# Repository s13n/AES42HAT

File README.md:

# AES42HAT

The AES42HAT is a Raspberry Pi compatible HAT with up to 4 channels of
AES3/AES42 interface. At present it is a work in progress.

AES3 is the stereo digital audio interface for professional applications, which
is compatible to some extent with SPDIF as used on consumer gear.

AES42 is building on AES3 to provide power and control for digital microphones.

Depending on what is fitted on the board, AES42HAT supports up to 4 stereo
channels of input/output, with or without SRC on input, and with or without
external synchronization.

Raspberry Pi models up to the Raspberry Pi 4B, and various clones, support only
one stereo channel in/out. The Raspberry Pi 5 supports the full set of 4 stereo
channels. The BeagleY-AI also supports 4 stereo channels in/out.

The 4 inputs and outputs are available on a header that supports the "Tascam
pinout" (or AES59 pinout) for a 25-pin SubD connector for multichannel digital
input/output. A standard IDC cable adapter between the header and the SubD
connector is needed.

## Build variants

The design supports different variants, depending on which parts are fitted on
the board. This allows a tradeoff between cost and feature set, depending on
user's needs.

See the schematics for the function blocks that can be omitted if desired. The
bare minimum consists of the parts that are shown outside of an optional block.

The Raspberry Pi uses the ID EEPROM to determine the build variant.

### Minimum build -- AES42HAT lite

The minimum build uses a DIX4192 for U10, and omits everything in the optional
blocks. It provides a stereo input/output in AES3 format, without SRC. It is
compatible with most Raspberry Pi models and some clones, provided they feature
a PCM interface on the standard pins, and a finely adjustable clock source on
GCLK0. It offers minimal cost for stereo applications that don't need AES42
support or SRC.

The lack of SRC means that there are only two sensible clocking options:

- The Raspberry Pi supplies the clock, and both input and output use it. This
  can be useful when an external device is connected, that synchronizes to the
  signal it receives from the AES42HAT.
- The output uses the clock derived from the received signal. This is useful
  when the external device is treated as the clock source, and the Raspberry is
  following it.

In both cases input and output use the same clock, i.e. they are synchronous to
each other.

The lack of a clock synthesizer means that the HAT is dependent on the Raspberry
Pi for a clock source. The original Raspberry Pi contains finely tunable PLLs
which can output a clock signal on GCLK0 that acts as a clock master. If a clone
doesn't support this, it won't work.

The lack of a control processor means that the DIX4192 is configured and
controlled directly by the Raspberry Pi through its SPI0 interface.

### Full-featured stereo interface -- AES42HAT stereo

This is the AES42HAT lite with an SRC4392 for U10, plus the clock synthesizer.

This adds the capability of using SRC on input, so the input clock can be
independent from the output clock. The presence of a clock synthesizer
eliminates the dependency on the Raspberry Pi clock generator, and adds a
separate wordclock input and output to support synchronization.

The clock syntheziser may also be slaved to a 10 MHz reference input as commonly
used in measurement equipment and frequency references. This can be used for
measurement purposes, or for creating audio clocks from GPS receivers and highly
stable oscillators.

The clock synthesizer is controlled by the Raspberry Pi through its I2C bus.

### Full-featured 8-channel interface -- AES42HAT octal

This adds 3 more stereo channels to the AES42HAT stereo to form a bidirectional
8-channel interface. SRC is supported on all channels by virtue of 3 more
SRC4392 chips, so that each input can run on its own clock, while all outputs
share a common clock generated by the local clock synthesizer.

The addition of more channels also requires the local control processor. The
SPI0 interface on the Raspberry Pi is no longer needed. All control is done via
the I2C bus, with the control processor managing the multiple channels.

Any of the input channels can be used as a synchronization source, instead of
the separate wordclock input.

The usage of a Raspberry 5 or a BeagleY-AI is needed to handle all the audio
channels.

### Full-featured 8-channel interface with AES42 support -- AES42HAT microphone

This adds AES42 compatible phantom power and remote control capability to all 4
stereo input channels of the AES42HAT octal. All synchronization modes of AES42
are supported, and the microphones can be remote controlled, independently for
each of the 4 inputs.

This requires a power supply that can deliver the necessary current for powering
the microphones in addition to the Raspberry Pi with the HAT. It is recommended
to use a 25W power supply capable of delivering 5A@5V to the Raspberry Pi 5.
Appropriate cooling should be provided.

The local control processor takes care of the AES42 specifics, and the Raspberry
Pi controls and monitors it via I2C.

If the goal is to merely power and control AES42 microphones, whose audio signal
is made available on the AES3 outputs, with no intent to process the audio with
the Raspberry Pi, then a cheaper/smaller Raspberry Pi can be used, for example a
Pi Zero 2. When intending to process the audio with the Raspberry Pi, use a
Raspberry Pi 5 or a BeagleY-AI.

## Function blocks

### Power Supply and Reset

The AES42HAT is powered through the HAT connector's 5V supply. Only the board ID
EEPROM (U3) is powered from the 3.3V supply on the HAT connector (J1). A dual
DC/DC converter (U4) generates local 3.3V and 1.8V rails for most of the
electronics on the board. The DC/DC converter is enabled by the 3.3V supply from
the HAT connector, so when the Raspberry Pi is powered down, the AES42HAT is
also powered down, even though the 5V rail may remain on.

The Raspberry Pi is responsible for lifting the RESET line after powerup,
otherwise the AES42HAT will remain in reset due to R5 pulling down the RESET
line. The ID EEPROM can be accessed regardless if the board is in reset or not.

### Local Control Processor (optional)

The 8-channel variants of the AES42HAT have a local control processor (U1)
fitted, which configures and controls the receivers and transmitters, and
handles the phantom powering, the remote control and the synchronization of the
AES42 interfaces.

The Raspberry Pi accesses the control processor primarily through I2C, using
pins 3&5 on the HAT connector. The Raspberry Pi controls this interface, and the
AES42HAT is the target. The communication protocol is TBD.

There is also a UART connection between the Raspberry Pi and the control
processor on pins 8&10. This connection can be used for updating the firmware of
the control processor from the Raspberry Pi. It may also be used during normal
operation for a console-like communication interface. The details are TBD.

There is an additional signal on Pin 26 of the HAT connector (REQ/ISP), which
serves two purposes:

- Upon release of RESET, the signal determines the boot mode of the control
  processor. When high, the control processor boots normally and executes its
  stored firmware. When low, it boots into a bootloader that can be used to
  update its firmware through the UART interface. Hence, to initiate firmware
  update, the Raspberry PI has to pull this signal low while releasing RESET.
- During normal operation, the signal is used as a service request signal from
  the AES42HAT to the Raspberry Pi. It is up to the Raspberry Pi to poll the
  signal, or arrange for an interrupt to be generated whenever the signal goes
  low. The control processor holds the interrupt active until the Raspberry Pi
  clears it through the I2C interface. The details are TBD.

When the control processor is fitted, the Raspberry Pi's own SPI interface on
HAT connector pins 19,21,23&24 is not used and must be disabled.

### Clock Synthesizer (optional)

The clock synthesizer supports generating arbitrary audio clock frequencies, and
to reference them to an external clock source. This provides considerable
flexibility in setting up the clocking structure of a system. The following
features are supported:

- Support for any sampling rate the Receivers/Transmitters are capable of (20 ..
  216 kHz). All transmitters use the same rate, and are synchronous to each
  other.
- Sampling rate can be finely tuned by software.
- An external 10 MHz reference can be connected to support synchronization from
  highly stable frequency sources (GPS receivers, OXCOs, Rubidium sources, ...).
  This can also help measurement applications. If no external reference is used,
  an internal 10 MHz crystal is used. The reference signal can be made available
  internally as the ACLK signal.
- Any one of the AES3 input signals can be used as the synchronization source.
- An external TTL wordclock signal can be connected to serve as a
  synchronization source.
- A TTL wordclock output is available.

All those features are controlled from software. The clock synthesizer is
connected to the I2C bus (HAT connector pins 3&5) that is controlled by the
Raspberry Pi. It produces two output clocks:

- The MCLK signal is the audio master clock from which the transmitters derive
  their output signal. The audio interface of the Raspberry Pi (PCM) is also
  driven from this clock, and operated in slave mode. The MCLK signal connects
  to pin 7 of the HAT interface. This allows the Raspberry Pi to supply the
  audio master clock instead of the clock synthesizer. The clock synthesizer's
  output must be switched off in this case (if it is fitted).
- The ACLK signal is typically driven by the 10 MHz reference clock signal. It
  can be used in the AES3 receivers as a reference signal for measuring incoming
  sampling rates.

The MCLK frequency should be between 10 and 25 MHz. For a single-speed sampling
rate up to a nominal 48 kHz, MCLK should be 512 * Fs. For a double-speed rate up
to 96 kHz it should be 256 * Fs. For a quad-speed rate up to 192 kHz it should
be 128 * Fs. The dividers in U10 must be set up to divide this down to the right
bit clock and word clock.

The clock synthesizer has a separate synchronization input that is driven by the
RCLK signal. Its use is optional, determined by software.

- If RCLK is not used, the 10 MHz signal is used as the reference, from which
  MCLK is derived directly using a fractional PLL.
- If RCLK is used, MCLK is derived from it by steering the fractional multiplier
  of the PLL to track the frequency of RCLK. This also reduces the jitter that
  may be present on RCLK. A wide frequency range on RCLK is supported (50 Hz ..
  30 MHz). Skipped pulses on RCLK can also be supported.

The RCLK signal can be fed from different sources:

- In the default case, it is fed from the external wordclock input. This is a
  TTL level signal that need not work at the wordclock frequency. It may be used
  to synchronize to a wide range of external frequency sources. The Raspberry Pi
  must enable it by driving the WIEN signal low.
- It can alternatively be fed from one of the receivers, using their RXCKO
  output. This output can be enabled to provide a clock signal derived from the
  incoming AES3 signal. It allows an incoming audio signal to be used as the
  synchronization source for the clock synthesizer. On 8-channel variants of
  AES42HAT, only one of four receiver chips can have this output enabled, or
  they will interfere with each other, potentially leading to damage. The output
  is disabled by default. Before enabling one of them, the Raspberry Pi must
  disable the external wordclock signal by driving the WIEN signal high.
- The Raspberry Pi can drive the RCLK signal using its GCLK2/GPIO6 signal on pin
  31 of the HAT connector. Both the wordclock input and the receiver RXCKO
  outputs must be disabled before the Raspberry Pi can activate this signal.

The clock syntheizer can be a CS2000 (obsolete), a CS2500 or a THAT7200. Its I²C
address is 0x4F (0x9E for write, 0x9F for read).

### AES Receivers/Transmitters

Decoding and encoding of the AES3 signal is done by U10 (on 8-channel variants
also U20, U30 and U40). There are three pin-compatible chips that can be fitted
alternatively:

- The **DIX4192** is a receiver and transmitter for one AES3 signal, including
  the balanced driver and receiver necessary for the physical interface.
- The **SRC4392** includes a sampling rate converter (SRC) that can be used with
  either the receiver or the transmitter, but is most useful with the receiver.
  Its other functions are the same as with the DIX4192, and the software
  interface is compatible.
- The **SRC4382** saves some cost by including a less accurate SRC that offers
  worse signal to noise. While this chip can be used, the cost savings are
  usually not worth it, and the AES42HAT will only use it upon special request.

Whichever chip is fitted, most of the functionality is the same. It has an
extensive register set for controlling the details of operation, which is
accessed through an SPI compatible interface.

When the local control processor is fitted, it is in control of the SPI
interface used to configure and control the receivers/transmitters.

The chips have flexible internal signal routing and clocking, which is set up
through the SPI control interface. Routing and clocking is set up as follows:

- U10 is the clock master on the PCM interface to the Raspberry Pi. Audio port A
  is configured in master mode and produces the BCLK and LR clock signals, with
  MCLK as the clock source. The BLS pin is configured as output.
- When fitted, U20, U30 & U40 operate their audio ports A&B in slave mode, so
  the BCKA, BCKB, LRCKA and LRCKB pins are inputs. The BLS pin is also
  configured as input.
- The transmitters within U10, U20, U30 and U40 are typically configured to be
  sourced from audio port A. The transmitter thereby sends an audio signal
  provided by the Raspberry Pi.
- Alternatively, the received input signal can be passed through to the output
  directly, using the pin multiplexers, bypassing the DIR and DIT blocks.
- The SRC is used with the receiver to convert the sampling rate of the received
  signal to the clock used on port A. If the input signal is known to be
  synchronous with this clock, the SRC can be omitted from the signal path.
- The ACLK signal (nominally 10 MHz) is available on the RXCKI signal, and can
  be used as a reference for the SRC to estimate the ratio. It can also be used
  as a reference clock for the DIR block. When the clock synthesizer is not
  fitted, the ACLK signal is not available, and the MCLK signal must be used as
  a reference.

Each receiver/transmitter has 4 GPO pins that have programmable functionality.
On the AES42HAT, they are used as follows:

- **GPO1** is used to enable phantom power for the AES42 input. If the AES42
  circuit is not fitted, the signal is unused. The output defaults to low after
  reset, thereby turning phantom power off.
- **GPO2** is used to select between two synchronization modes of AES42. This is
  only relevant when phantom power is switched on. A low signal selects mode 2,
  which is the default after reset.
- **GPO3** is connected to the control processor, and is intended to carry the
  reconstructed wordclock signal from the receiver ("Receiver Internal Sync
  Clock"). If the control processor is not fitted, the signal is unused.
- **GPO4** is connected to the control processor, and is intended to carry the
  received U-bit ("Receiver User Data Bit"), giving the control processor an
  alternate way to process the incoming user bit. If the control processor is
  not fitted, the signal is unused.

If the intended functionality of GPO3&4 is not required, other signals may be
chosen to be fed to the control processor.

Each receiver/transmitter can generate an interrupt signal. The interrupt signal
is handled by the control processor, if it is fitted. Otherwise the interrupt
from U10 is fed to the Raspberry Pi on HAT connector pin 26.

### AES42 Phantom Supply and Remote Control

AES42 defines a way of powering a connected microphone using a 10 V phantom
power scheme. Additionally, remote control signals can be sent to the microphone
by modulating them on top of the phantom power. The "AES42HAT microphone", the
fully featured variant, supports both.

Phantom power is generated by a DC/DC converter (U51, U61, U71, U81). Each input
can be powered separately, controlled by GPO1 of the respective
receiver/transmitter. The DC/DC converter works from the +5V rail, and each
circuit potentially draws up to 600mA from this rail, depending on the load
represented by the microphone that is connected. The power supply used must be
able to deliver this amount of current.

The control processor can monitor the phantom voltage through signals PVx, so it
can diagnose short circuits or overload.

Remote control using AES42 Mode 2 is handled by raising the phantom voltage for
each pulse generated. This is achieved by temporarily switching the DC/DC
converter to output 12 V instead of 10 V. Edge speed is shaped by an additional
driver (U52, U62, U72, U82).

Mode 3 is supported by a different circuit built from a signal transformer (L50,
L60, L70, L80) driven by a bandpass amplifier (U53, U63, U73, U83). It is based
on a clock signal WCLK generated by the control processor.

For both modes, the modulating signal (MODx) is generated by the control
processor. Switches (U50, U60, U70, U80) are used to select between the two
modes, depending on signals M3x sourced by GPO2 of the receiver/transmitter.

An LED shows the presence of phantom power on each channel. Its brightness is
modulated by the remote control pulses.

### Dependencies Between Optional Function Blocks

The control processor must be fitted if any of U20, U30 or U40 are fitted. It
must also be fitted when the AES42 circuitry is fitted.

The clock synthesizer is controlled by the Raspberry Pi and can be fitted
without the control processor. The clock synthesizer is independent from any
other function block and can be fitted or omitted, regardless of which other
options are fitted. However, if not fitted, the Raspberry Pi must supply the
audio master clock (GCLK0).

## Support for Raspberry Pi Variants and Clones

The AES42HAT is fully compatible with the Raspberry Pi 5, including support for
up to 8 channels of audio input and output.

Previous models of the Raspberry Pi up to the 4B only support stereo audio. The
8-channel variants of AES42HAT can therefore not be fully supported, i.e. the
audio signals of the additional channels can't be accessed by the Raspberry Pi.
The additional channels can be controlled and configured, however, so it is
possible to support use cases where the audio signals need not be touched by the
Raspberry Pi (for example using pass-through from input to output, without or
with SRC).

Raspberry Pi clones may or may not support the PCM interface, so it is up to the
user to check compatibility. In many cases only stereo is supported, if at all.

### BeagleY-AI

The BeagleY-AI is a clone that can support all 8 channels, albeit with some
special arrangements. The pin assignment for the PCM interface is only partly
compatible with the Raspberry Pi 5, and AES42HAT contains some additional wiring
to make up for the difference.

With the BeagleY-AI, the McASP0 is used for all the input signals with up to 8
channels. The output channels are generated by McASP1 and McASP2 in SPDIF
transmit mode. The latter is necessary because of limitations of clock signal
connectivity. The input multiplexers in the receivers/transmitters are used to
route the output signals directly to the balanced line driver, bypassing the DIT
block. To deal with wiring differences for input channels, audio port B is used
on U30 and U40.

### ESP32-P4 Function Evaluation Board

The Espressif ESP32-P4 is a microcontroller with a dual-core RISC-V CPU and a
rich set of peripherals, including I2S and 100 MBit/s Ethernet. It appears to
have some potential for a very low cost platform for low-end networked audio
devices, below the price point of a Linux-based solution. Its evaluation board
has a set of GPIO signals routed to a Raspberry Pi HAT connector. This opens the
possibility to use the AES42HAT as an audio interface.

The ESP32-P4 has 3 I2S function blocks that can be freely assigned to GPIO pins,
and it includes a PLL dedicated for audio. It therefore should be able to work
with the AES42HAT directly, with no need for a wiring change. At the time of
writing, the information available for the ESP32-P4 is sparse, hence the
suitability is somewhat unclear at this point, but it certainly looks promising.

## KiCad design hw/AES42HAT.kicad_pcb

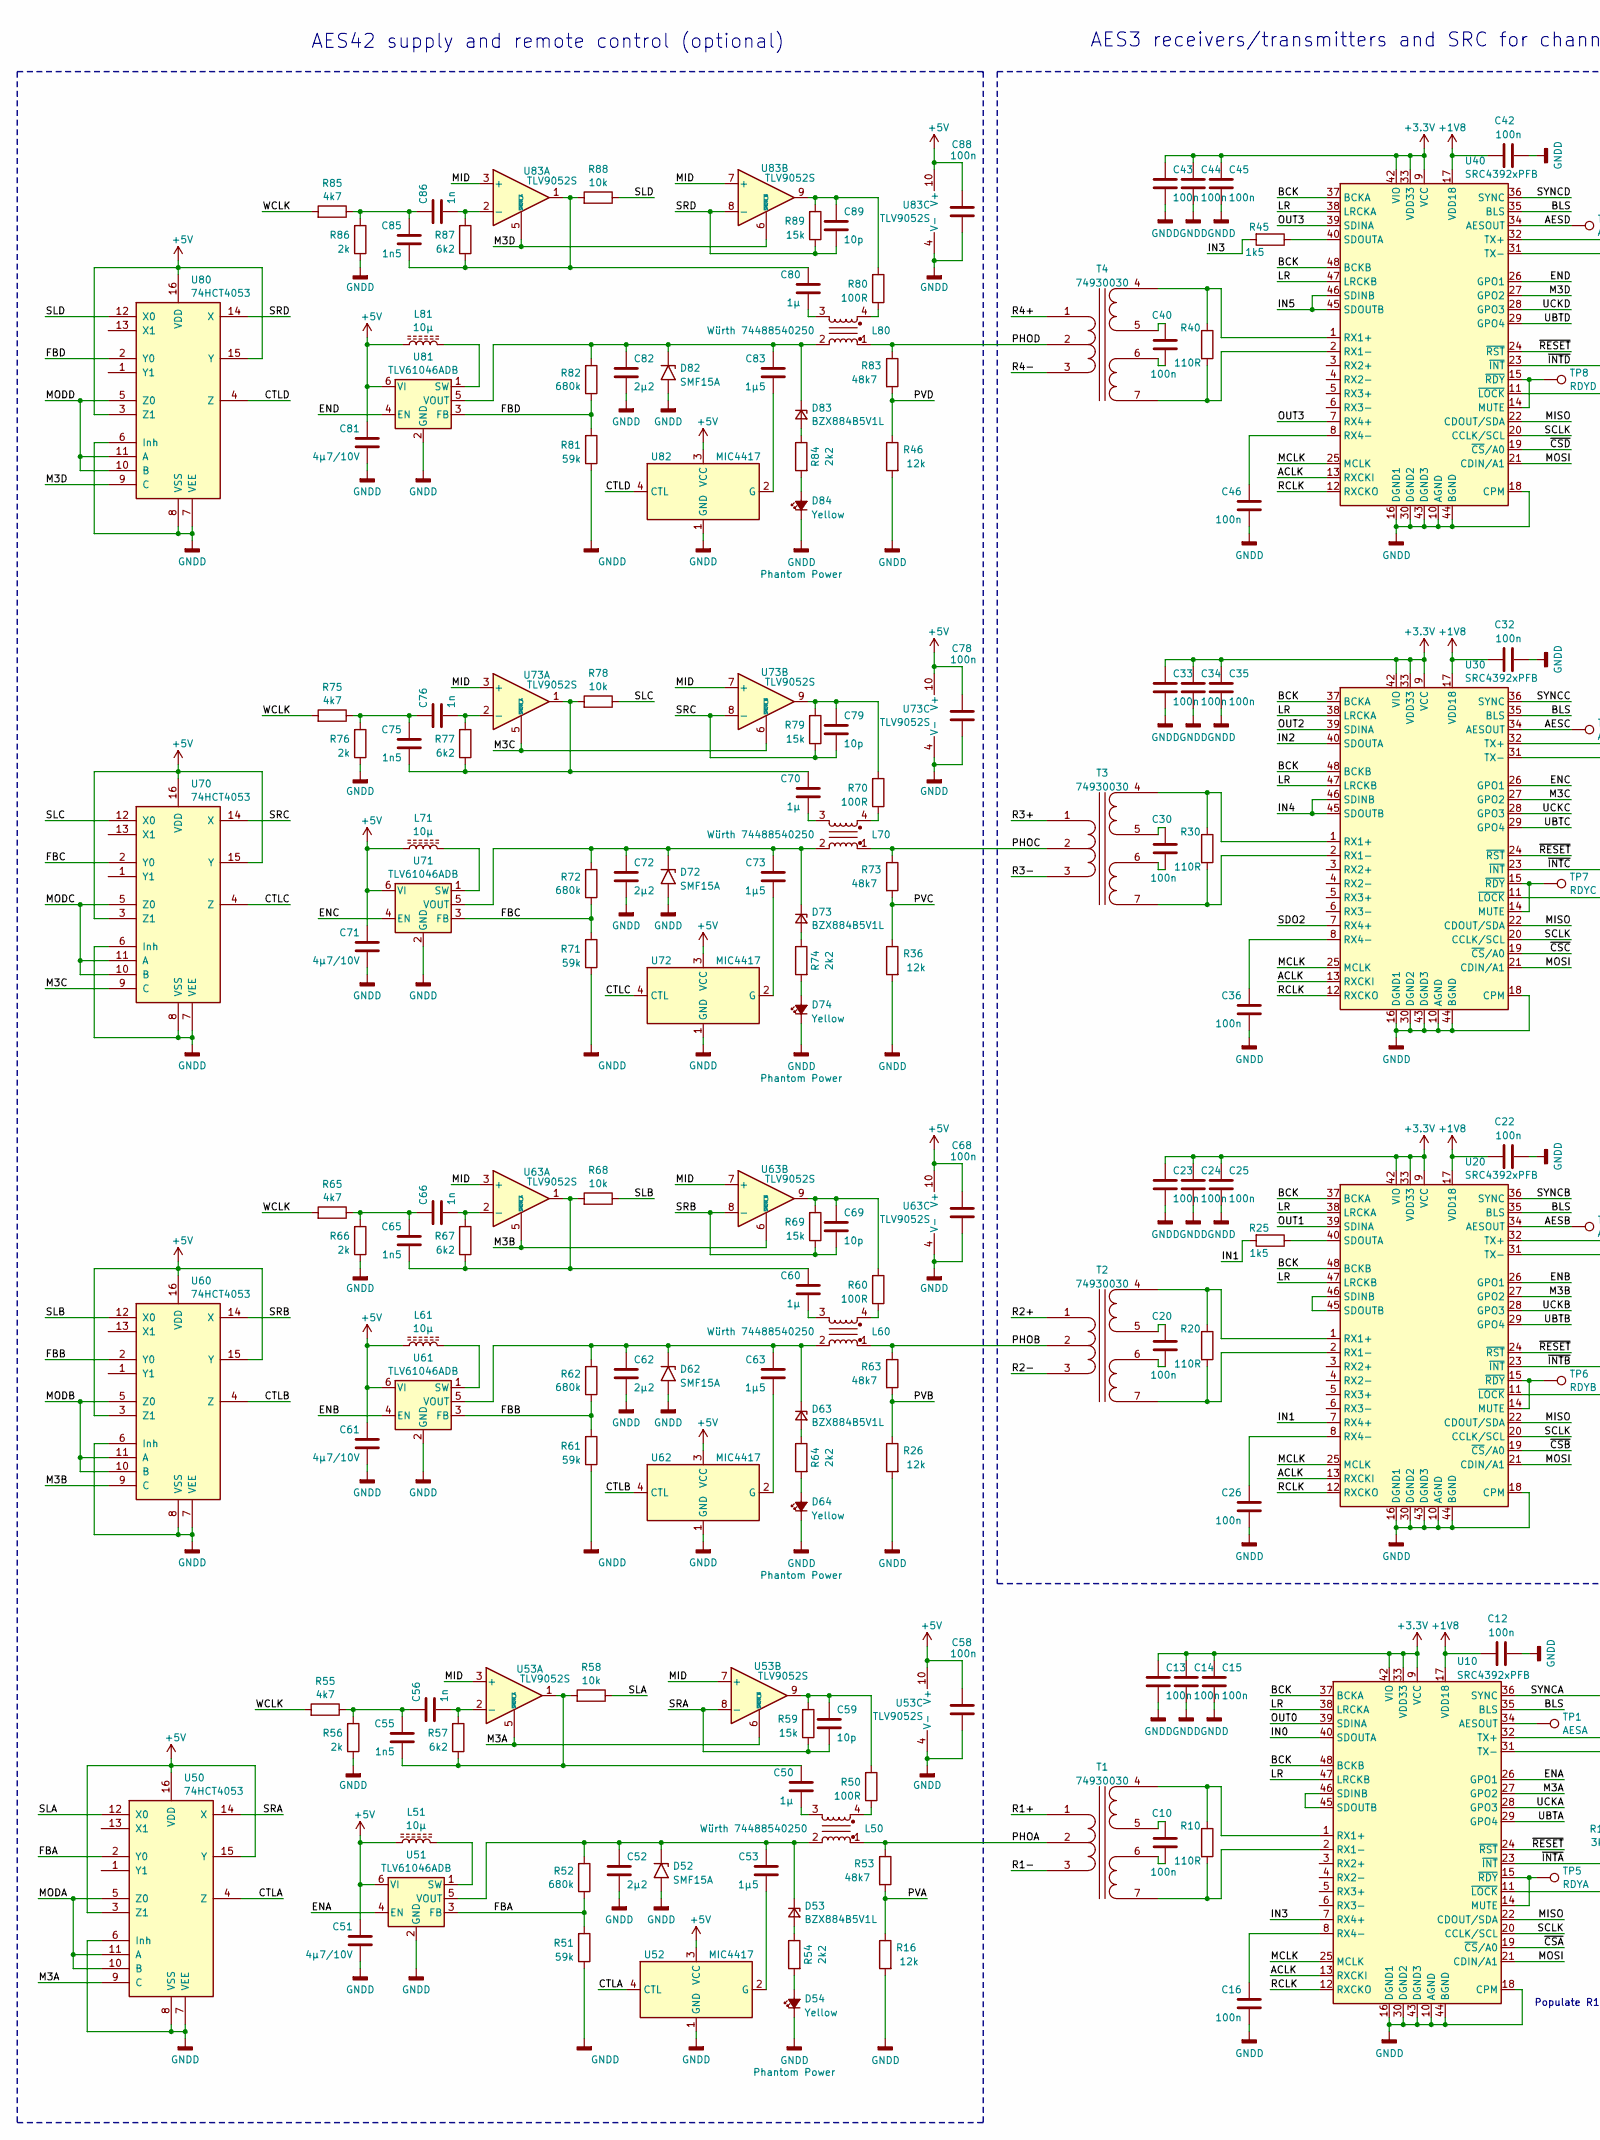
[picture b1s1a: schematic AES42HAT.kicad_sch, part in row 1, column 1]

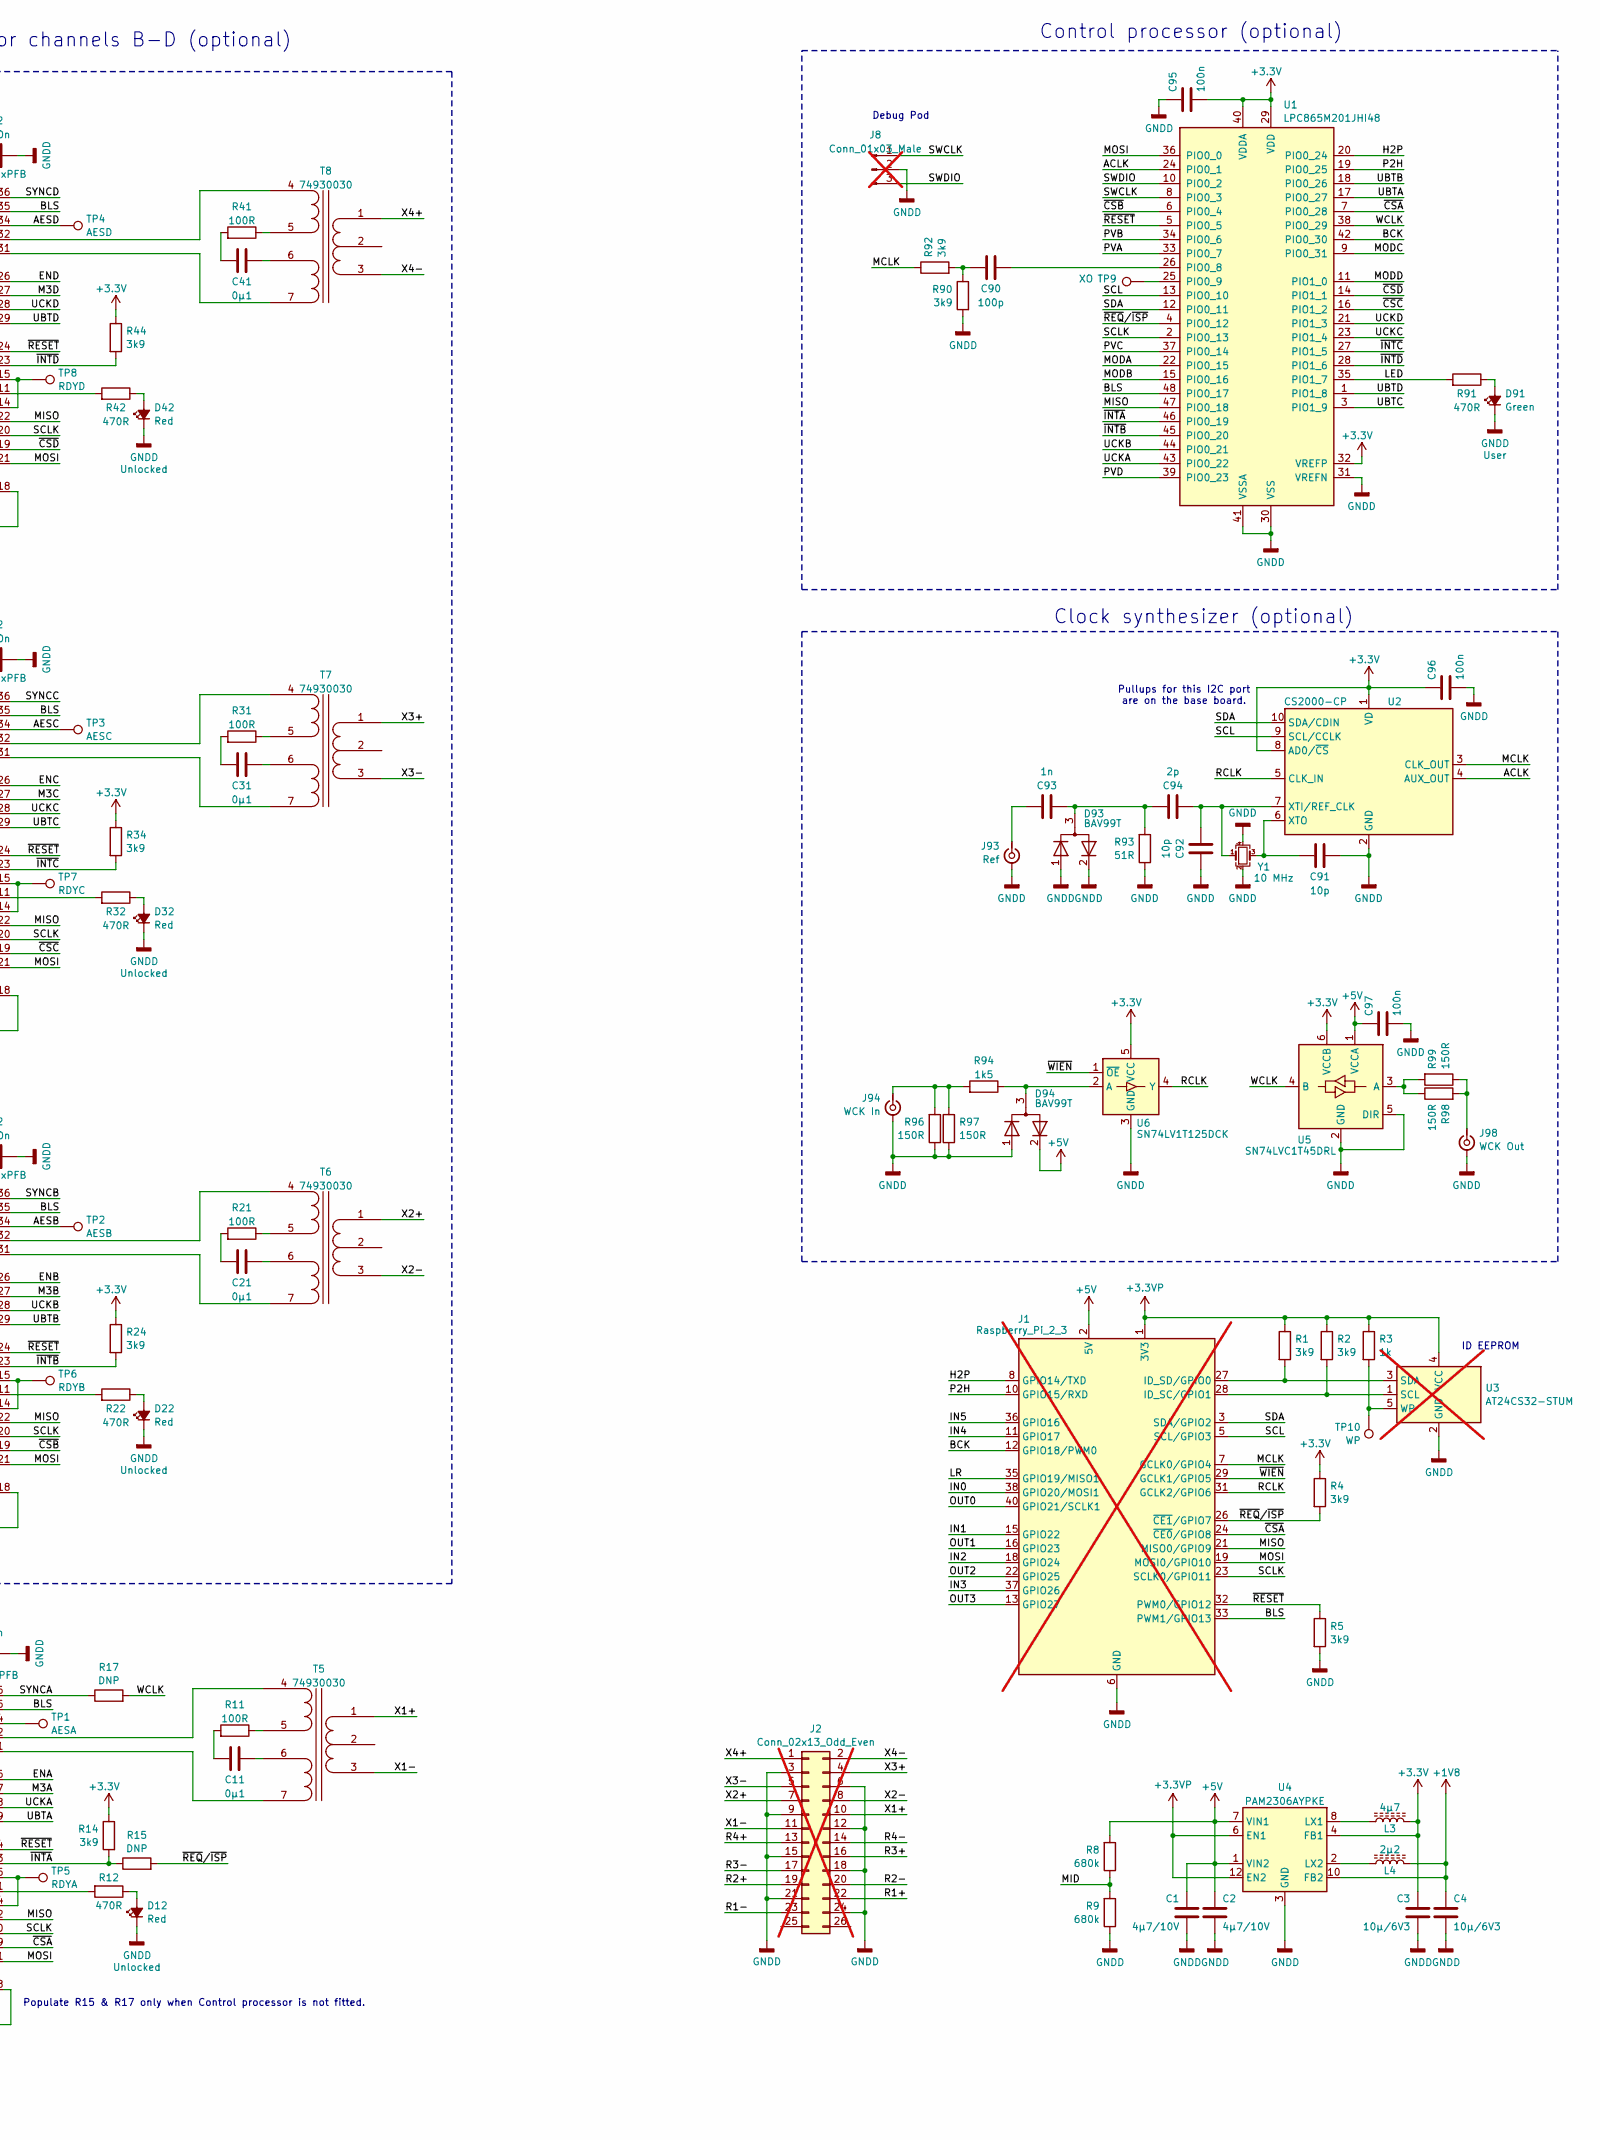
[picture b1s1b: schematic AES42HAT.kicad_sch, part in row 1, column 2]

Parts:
C1, C2, C51, C61, C71, C81: 4µ7/10V; C_0603_1608Metric
C3, C4: 10µ/6V3; C_0603_1608Metric
C10, C12, C13, C14, C15, C16, C20, C22, C23, C24, C25, C26, C30, C32, C33, C34, C35, C36, C40, C42, C43, C44, C45, C46, C58, C68, C78, C88, C95, C96, C97: 100n; C_0402_1005Metric
C11, C21, C31, C41: 0µ1; C_0402_1005Metric
C50, C60, C70, C80: 1µ; C_0402_1005Metric
C52, C62, C72, C82: 2µ2; C_0603_1608Metric
C53, C63, C73, C83: 1µ5; C_0603_1608Metric
C55, C65, C75, C85: 1n5; C_0402_1005Metric
C56, C66, C76, C86, C93: 1n; C_0402_1005Metric
C59, C69, C79, C89, C91, C92: 10p; C_0402_1005Metric
C90: 100p; C_0402_1005Metric
C94: 2p; C_0402_1005Metric
D12, D22, D32, D42: Red; LED_0402_1005Metric
D52, D62, D72, D82: SMF15A; D_SMF
D53, D63, D73, D83: BZX884B5V1L; D_0402_1005Metric
D54, D64, D74, D84: Yellow; LED_0402_1005Metric
D91: Green; LED_0402_1005Metric
D93, D94: BAV99T; SOT-523
J1: Raspberry_Pi_2_3; Raspberry_Pi_HAT; not fitted
J2: Conn_02x13_Odd_Even; IDC-Header_2x13_P2.54mm_Vertical; not fitted
J8: Conn_01x03_Male; PinHeader_1x03_P2.54mm_Vertical; not fitted
J93: Ref; U.FL_Hirose_U.FL-R-SMT-1_Vertical
J94: WCK In; U.FL_Hirose_U.FL-R-SMT-1_Vertical
J98: WCK Out; U.FL_Hirose_U.FL-R-SMT-1_Vertical
L3: 4µ7; L_Wuerth_MAPI-2512
L4: 2µ2; L_Wuerth_MAPI-2010
L50, L60, L70, L80: Würth 74488540250; Coupled_Choke_Wuerth_74488540250
L51, L61, L71, L81: 10µ; L_Wuerth_MAPI-2512
R1, R2, R4, R5, R14, R24, R34, R44, R90, R92: 3k9; R_0402_1005Metric
R3: 1k; R_0402_1005Metric
R8, R9, R52, R62, R72, R82: 680k; R_0402_1005Metric
R10, R20, R30, R40: 110R; R_0402_1005Metric
R11, R21, R31, R41, R50, R60, R70, R80: 100R; R_0402_1005Metric
R12, R22, R32, R42, R91: 470R; R_0402_1005Metric
R15, R17: DNP; R_0402_1005Metric
R16, R26, R36, R46: 12k; R_0402_1005Metric
R25, R45, R94: 1k5; R_0402_1005Metric
R51, R61, R71, R81: 59k; R_0402_1005Metric
R53, R63, R73, R83: 48k7; R_0402_1005Metric
R54, R64, R74, R84: 2k2; R_0402_1005Metric
R55, R65, R75, R85: 4k7; R_0402_1005Metric
R56, R66, R76, R86: 2k; R_0402_1005Metric
R57, R67, R77, R87: 6k2; R_0402_1005Metric
R58, R68, R78, R88: 10k; R_0402_1005Metric
R59, R69, R79, R89: 15k; R_0402_1005Metric
R93: 51R; R_0402_1005Metric
R96, R97, R98, R99: 150R; R_0402_1005Metric
T1, T2, T3, T4, T5, T6, T7, T8: 74930030; Transformer_Wuerth_74930030
TP1: AESA; TestPoint_Pad_D1.0mm
TP2: AESB; TestPoint_Pad_D1.0mm
TP3: AESC; TestPoint_Pad_D1.0mm
TP4: AESD; TestPoint_Pad_D1.0mm
TP5: RDYA; TestPoint_Pad_D1.0mm
TP6: RDYB; TestPoint_Pad_D1.0mm
TP7: RDYC; TestPoint_Pad_D1.0mm
TP8: RDYD; TestPoint_Pad_D1.0mm
TP9: XO; TestPoint_Pad_D1.0mm
TP10: WP; TestPoint_Pad_D1.0mm
U1: LPC865M201JHI48; QFN-48-1EP_7x7mm_P0.5mm_EP5.1x5.1mm
U2: CS2000-CP; MSOP-10_3x3mm_P0.5mm
U3: AT24CS32-STUM; SOT-23-5; not fitted
U4: PAM2306AYPKE; WDFN-12-1EP_3x3mm_P0.45mm_EP1.7x2.5mm
U5: SN74LVC1T45DRL; SOT-563
U6: SN74LV1T125DCK; SOT-353_SC-70-5
U10, U20, U30, U40: SRC4392xPFB; TQFP-48_7x7mm_P0.5mm
U50, U60, U70, U80: 74HCT4053; TSSOP-16_4.4x5mm_P0.65mm
U51, U61, U71, U81: TLV61046ADB; SOT-23-6
U52, U62, U72, U82: MIC4417; SOT-143
U53, U63, U73, U83: TLV9052S; MSOP-10_3x3mm_P0.5mm
Y1: 10 MHz; Crystal_SMD_3225-4Pin_3.2x2.5mm

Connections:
+1V8: C4.1, C12.1, C22.1, C32.1, C42.1, L4.2, U4.10 (FB2), U10.17 (VDD18), U20.17 (VDD18), U30.17 (VDD18), U40.17 (VDD18)
+3.3V: C3.1, C13.1, C14.1, C15.1, C23.1, C24.1, C25.1, C33.1, C34.1, C35.1, C43.1, C44.1, C45.1, C95.2, C96.1, J1.5 (VCC), L3.2, R4.1, R14.1, R24.1, R34.1, R44.1, U1.29 (VDD), U1.32 (VREFP), U1.40 (VDDA), U2.1 (VD), U2.8 (AD0/~CS), U4.4 (FB1), U5.6 (VCCB), U6.5 (VCC), U10.9 (VCC), U10.33 (VDD33), U10.42 (VIO), U20.9 (VCC), U20.33 (VDD33), U20.42 (VIO), U30.9 (VCC), U30.33 (VDD33), U30.42 (VIO), U40.9 (VCC), U40.33 (VDD33), U40.42 (VIO)
+3.3VP: J1.1 (3V3), J1.17 (3V3), R1.1, R2.1, R3.1, U3.4 (VCC), U4.6 (EN1), U4.12 (EN2)
/ACLK: U1.24 (PIO0_1), U2.4 (AUX_OUT), U10.13 (RXCKI), U20.13 (RXCKI), U30.13 (RXCKI), U40.13 (RXCKI)
/AESB: TP2.1, U20.34 (AESOUT)
/AESC: TP3.1, U30.34 (AESOUT)
/AESD: TP4.1, U40.34 (AESOUT)
/BCK: J1.12 (GPIO18/PWM0), U1.42 (PIO0_30), U10.37 (BCKA), U10.48 (BCKB), U20.37 (BCKA), U20.48 (BCKB), U30.37 (BCKA), U30.48 (BCKB), U40.37 (BCKA), U40.48 (BCKB)
/BLS: J1.33 (PWM1/GPIO13), U1.48 (PIO0_17), U10.35 (BLS), U20.35 (BLS), U30.35 (BLS), U40.35 (BLS)
/CTLA: U50.4 (Z), U52.4 (CTL)
/CTLB: U60.4 (Z), U62.4 (CTL)
/CTLC: U70.4 (Z), U72.4 (CTL)
/CTLD: U80.4 (Z), U82.4 (CTL)
/ENA: U10.26 (GPO1), U51.4 (EN)
/ENB: U20.26 (GPO1), U61.4 (EN)
/ENC: U30.26 (GPO1), U71.4 (EN)
/END: U40.26 (GPO1), U81.4 (EN)
/FBA: R51.2, R52.1, U50.2 (Y0), U51.3 (FB)
/FBB: R61.2, R62.1, U60.2 (Y0), U61.3 (FB)
/FBC: R71.2, R72.1, U70.2 (Y0), U71.3 (FB)
/FBD: R81.2, R82.1, U80.2 (Y0), U81.3 (FB)
/H2P: J1.8 (GPIO14/TXD), U1.20 (PIO0_24)
/IN0: J1.38 (GPIO20/MOSI1), U10.40 (SDOUTA)
/IN1: J1.15 (GPIO22), R25.2, U20.7 (RX4+)
/IN2: J1.18 (GPIO24), U30.40 (SDOUTA)
/IN3: J1.37 (GPIO26), R45.2, U10.7 (RX4+)
/IN4: J1.11 (GPIO17), U30.45 (SDOUTB), U30.46 (SDINB)
/IN5: J1.36 (GPIO16), U40.45 (SDOUTB), U40.46 (SDINB)
/LED: R91.2, U1.35 (PIO1_7)
/LR: J1.35 (GPIO19/MISO1), U10.38 (LRCKA), U10.47 (LRCKB), U20.38 (LRCKA), U20.47 (LRCKB), U30.38 (LRCKA), U30.47 (LRCKB), U40.38 (LRCKA), U40.47 (LRCKB)
/M3A: U10.27 (GPO2), U50.9 (C), U53.5 (~SHDN_A), U53.6 (~SHDN_B)
/M3B: U20.27 (GPO2), U60.9 (C), U63.5 (~SHDN_A), U63.6 (~SHDN_B)
/M3C: U30.27 (GPO2), U70.9 (C), U73.5 (~SHDN_A), U73.6 (~SHDN_B)
/M3D: U40.27 (GPO2), U80.9 (C), U83.5 (~SHDN_A), U83.6 (~SHDN_B)
/MCLK: J1.7 (GCLK0/GPIO4), R92.1, U2.3 (CLK_OUT), U10.25 (MCLK), U20.25 (MCLK), U30.25 (MCLK), U40.25 (MCLK)
/MID: R8.1, R9.2, U53.3 (+), U53.7 (+), U63.3 (+), U63.7 (+), U73.3 (+), U73.7 (+), U83.3 (+), U83.7 (+)
/MISO: J1.21 (MISO0/GPIO9), U1.47 (PIO0_18), U10.22 (CDOUT/SDA), U20.22 (CDOUT/SDA), U30.22 (CDOUT/SDA), U40.22 (CDOUT/SDA)
/MODA: U1.22 (PIO0_15), U50.5 (Z0), U50.10 (B), U50.11 (A)
/MODB: U1.15 (PIO0_16), U60.5 (Z0), U60.10 (B), U60.11 (A)
/MODC: U1.9 (PIO0_31), U70.5 (Z0), U70.10 (B), U70.11 (A)
/MODD: U1.11 (PIO1_0), U80.5 (Z0), U80.10 (B), U80.11 (A)
/MOSI: J1.19 (MOSI0/GPIO10), U1.36 (PIO0_0), U10.21 (CDIN/A1), U20.21 (CDIN/A1), U30.21 (CDIN/A1), U40.21 (CDIN/A1)
/OUT0: J1.40 (GPIO21/SCLK1), U10.39 (SDINA)
/OUT1: J1.16 (GPIO23), U20.39 (SDINA)
/OUT2: J1.22 (GPIO25), U30.39 (SDINA)
/OUT3: J1.13 (GPIO27), U40.7 (RX4+), U40.39 (SDINA)
/P2H: J1.10 (GPIO15/RXD), U1.19 (PIO0_25)
/PHOA: L50.1, R53.1, T1.2 (PM)
/PHOB: L60.1, R63.1, T2.2 (PM)
/PHOC: L70.1, R73.1, T3.2 (PM)
/PHOD: L80.1, R83.1, T4.2 (PM)
/PVA: R16.1, R53.2, U1.33 (PIO0_7)
/PVB: R26.1, R63.2, U1.34 (PIO0_6)
/PVC: R36.1, R73.2, U1.37 (PIO0_14)
/PVD: R46.1, R83.2, U1.39 (PIO0_23)
/R1+: J2.22, T1.1 (IN+)
/R1-: J2.23, T1.3 (IN-)
/R2+: J2.19, T2.1 (IN+)
/R2-: J2.20, T2.3 (IN-)
/R3+: J2.16, T3.1 (IN+)
/R3-: J2.17, T3.3 (IN-)
/R4+: J2.13, T4.1 (IN+)
/R4-: J2.14, T4.3 (IN-)
/SCL: J1.5 (SCL/GPIO3), U1.13 (PIO0_10), U2.9 (SCL/CCLK)
/SCLK: J1.23 (SCLK0/GPIO11), U1.2 (PIO0_13), U10.20 (CCLK/SCL), U20.20 (CCLK/SCL), U30.20 (CCLK/SCL), U40.20 (CCLK/SCL)
/SDA: J1.3 (SDA/GPIO2), U1.12 (PIO0_11), U2.10 (SDA/CDIN)
/SDO2: U30.7 (RX4+)
/SLA: R58.1, U50.12 (X0)
/SLB: R68.1, U60.12 (X0)
/SLC: R78.1, U70.12 (X0)
/SLD: R88.1, U80.12 (X0)
/SRA: C59.2, R59.1, U50.14 (X), U53.8 (-)
/SRB: C69.2, R69.1, U60.14 (X), U63.8 (-)
/SRC: C79.2, R79.1, U70.14 (X), U73.8 (-)
/SRD: C89.2, R89.1, U80.14 (X), U83.8 (-)
/SWCLK: J8.1, U1.8 (PIO0_3)
/SWDIO: J8.3, U1.10 (PIO0_2)
/SYNCA: R17.1, U10.36 (SYNC)
/SYNCB: U20.36 (SYNC)
/SYNCC: U30.36 (SYNC)
/SYNCD: U40.36 (SYNC)
/UBTA: U1.17 (PIO0_27), U10.29 (GPO4)
/UBTB: U1.18 (PIO0_26), U20.29 (GPO4)
/UBTC: U1.3 (PIO1_9), U30.29 (GPO4)
/UBTD: U1.1 (PIO1_8), U40.29 (GPO4)
/UCKA: U1.43 (PIO0_22), U10.28 (GPO3)
/UCKB: U1.44 (PIO0_21), U20.28 (GPO3)
/UCKC: U1.23 (PIO1_4), U30.28 (GPO3)
/UCKD: U1.21 (PIO1_3), U40.28 (GPO3)
/WCLK: R17.2, R55.2, R65.2, R75.2, R85.2, U1.38 (PIO0_29), U5.4 (B)
/X1+: J2.10, T5.1 (IN+)
/X1-: J2.11, T5.3 (IN-)
/X2+: J2.7, T6.1 (IN+)
/X2-: J2.8, T6.3 (IN-)
/X3+: J2.4, T7.1 (IN+)
/X3-: J2.5, T7.3 (IN-)
/X4+: J2.1, T8.1 (IN+)
/X4-: J2.2, T8.3 (IN-)
/~CSA: J1.24 (~CE0/GPIO8), U1.7 (PIO0_28), U10.19 (~CS/A0)
/~CSB: U1.6 (PIO0_4), U20.19 (~CS/A0)
/~CSC: U1.16 (PIO1_2), U30.19 (~CS/A0)
/~CSD: U1.14 (PIO1_1), U40.19 (~CS/A0)
/~INTA: R14.2, R15.1, U1.46 (PIO0_19), U10.23 (~INT)
/~INTB: R24.2, U1.45 (PIO0_20), U20.23 (~INT)
/~INTC: R34.2, U1.27 (PIO1_5), U30.23 (~INT)
/~INTD: R44.2, U1.28 (PIO1_6), U40.23 (~INT)
/~REQ/~ISP: J1.26 (~CE1/GPIO7), R4.2, R15.2, U1.4 (PIO0_12)
/~RESET: J1.32 (PWM0/GPIO12), R5.1, U1.5 (PIO0_5), U10.24 (~RST), U20.24 (~RST), U30.24 (~RST), U40.24 (~RST)
/~WIEN: J1.29 (GCLK1/GPIO5), U6.1 (~OE)
GNDD: C1.2, C2.2, C3.2, C4.2, C12.2, C13.2, C14.2, C15.2, C16.2, C22.2, C23.2, C24.2, C25.2, C26.2, C32.2, C33.2, C34.2, C35.2, C36.2, C42.2, C43.2, C44.2, C45.2, C46.2, C51.2, C52.2, C58.2, C61.2, C62.2, C68.2, C71.2, C72.2, C78.2, C81.2, C82.2, C88.2, C91.1, C92.2, C95.1, C96.2, C97.2, D12.1 (K), D22.1 (K), D32.1 (K), D42.1 (K), D52.2 (A2), D54.1 (K), D62.2 (A2), D64.1 (K), D72.2 (A2), D74.1 (K), D82.2 (A2), D84.1 (K), D91.1 (K), D93.1 (K), D93.2 (K), D94.1 (K), J1.6 (GND), J1.9 (GND), J1.14 (GND), J1.20 (GND), J1.25 (GND), J1.30 (GND), J1.34 (GND), J1.39 (GND), J2.3, J2.6, J2.9, J2.12, J2.15, J2.18, J2.21, J2.24, J8.2, J93.2 (Ext), J94.2 (Ext), J98.2 (Ext), R5.2, R9.1, R16.2, R26.2, R36.2, R46.2, R51.1, R56.1, R61.1, R66.1, R71.1, R76.1, R81.1, R86.1, R90.2, R93.1, R96.1, R97.1, U1.30 (VSS), U1.31 (VREFN), U1.41 (VSSA), U2.2 (GND), U3.2 (GND), U4.3 (GND), U4.9 (GND), U4.13 (GND), U5.2 (GND), U5.5 (DIR), U6.3 (GND), U10.10 (AGND), U10.16 (DGND1), U10.18 (CPM), U10.30 (DGND2), U10.43 (DGND3), U10.44 (BGND), U20.10 (AGND), U20.16 (DGND1), U20.18 (CPM), U20.30 (DGND2), U20.43 (DGND3), U20.44 (BGND), U30.10 (AGND), U30.16 (DGND1), U30.18 (CPM), U30.30 (DGND2), U30.43 (DGND3), U30.44 (BGND), U40.10 (AGND), U40.16 (DGND1), U40.18 (CPM), U40.30 (DGND2), U40.43 (DGND3), U40.44 (BGND), U50.6 (Inh), U50.7 (VEE), U50.8 (VSS), U51.2 (GND), U52.1 (GND), U53.4 (V-), U53.11 (V-), U60.6 (Inh), U60.7 (VEE), U60.8 (VSS), U61.2 (GND), U62.1 (GND), U63.4 (V-), U63.11 (V-), U70.6 (Inh), U70.7 (VEE), U70.8 (VSS), U71.2 (GND), U72.1 (GND), U73.4 (V-), U73.11 (V-), U80.6 (Inh), U80.7 (VEE), U80.8 (VSS), U81.2 (GND), U82.1 (GND), U83.4 (V-), U83.11 (V-), Y1.2, Y1.4
unnamed: C11.2, R11.2
unnamed: C21.2, R21.2
unnamed: C31.2, R31.2
unnamed: C41.2, R41.2
unnamed: C50.1, C55.2, R57.1, R58.2, U53.1
unnamed: C50.2, L50.3
unnamed: C55.1, C56.1, R55.1, R56.2
unnamed: C59.1, R50.2, R59.2, U53.9
unnamed: C60.1, C65.2, R67.1, R68.2, U63.1
unnamed: C60.2, L60.3
unnamed: C65.1, C66.1, R65.1, R66.2
unnamed: C69.1, R60.2, R69.2, U63.9
unnamed: C70.1, C75.2, R77.1, R78.2, U73.1
unnamed: C70.2, L70.3
unnamed: C75.1, C76.1, R75.1, R76.2
unnamed: C79.1, R70.2, R79.2, U73.9
unnamed: C80.1, C85.2, R87.1, R88.2, U83.1
unnamed: C80.2, L80.3
unnamed: C85.1, C86.1, R85.1, R86.2
unnamed: C89.1, R80.2, R89.2, U83.9
unnamed: C90.2, R90.1, R92.2
unnamed: D12.2 (A), R12.1
unnamed: D22.2 (A), R22.1
unnamed: D32.2 (A), R32.1
unnamed: D42.2 (A), R42.1
unnamed: C52.1, C53.1, D52.1 (A1), D53.1 (K), L50.2, R52.2, U51.5 (VOUT)
unnamed: D53.2 (A), R54.1
unnamed: D54.2 (A), R54.2
unnamed: C62.1, C63.1, D62.1 (A1), D63.1 (K), L60.2, R62.2, U61.5 (VOUT)
unnamed: D63.2 (A), R64.1
unnamed: D64.2 (A), R64.2
unnamed: C72.1, C73.1, D72.1 (A1), D73.1 (K), L70.2, R72.2, U71.5 (VOUT)
unnamed: D73.2 (A), R74.1
unnamed: D74.2 (A), R74.2
unnamed: C82.1, C83.1, D82.1 (A1), D83.1 (K), L80.2, R82.2, U81.5 (VOUT)
unnamed: D83.2 (A), R84.1
unnamed: D84.2 (A), R84.2
unnamed: D91.2 (A), R91.1
unnamed: C93.1, C94.2, D93.3 (A), R93.2
unnamed: D94.3 (A), R94.1, U6.2 (A)
unnamed: J1.28 (ID_SC/GPIO1), R2.2, U3.1 (SCL)
unnamed: J1.27 (ID_SD/GPIO0), R1.2, U3.3 (SDA)
unnamed: C93.2, J93.1 (In)
unnamed: J94.1 (In), R94.2, R96.2, R97.2
unnamed: J98.1 (In), R98.2, R99.1
unnamed: L50.4, R50.1
unnamed: L60.4, R60.1
unnamed: L70.4, R70.1
unnamed: L80.4, R80.1
unnamed: R10.1, T1.4 (OUT1A), U10.1 (RX1+)
unnamed: C10.1, T1.5 (OUT1B)
unnamed: C10.2, T1.6 (OUT2A)
unnamed: R10.2, T1.7 (OUT2B), U10.2 (RX1-)
unnamed: R20.1, T2.4 (OUT1A), U20.1 (RX1+)
unnamed: C20.1, T2.5 (OUT1B)
unnamed: C20.2, T2.6 (OUT2A)
unnamed: R20.2, T2.7 (OUT2B), U20.2 (RX1-)
unnamed: R30.1, T3.4 (OUT1A), U30.1 (RX1+)
unnamed: C30.1, T3.5 (OUT1B)
unnamed: C30.2, T3.6 (OUT2A)
unnamed: R30.2, T3.7 (OUT2B), U30.2 (RX1-)
unnamed: R40.1, T4.4 (OUT1A), U40.1 (RX1+)
unnamed: C40.1, T4.5 (OUT1B)
unnamed: C40.2, T4.6 (OUT2A)
unnamed: R40.2, T4.7 (OUT2B), U40.2 (RX1-)
unnamed: T5.4 (OUT1A), U10.32 (TX+)
unnamed: R11.1, T5.5 (OUT1B)
unnamed: C11.1, T5.6 (OUT2A)
unnamed: T5.7 (OUT2B), U10.31 (TX-)
unnamed: T6.4 (OUT1A), U20.32 (TX+)
unnamed: R21.1, T6.5 (OUT1B)
unnamed: C21.1, T6.6 (OUT2A)
unnamed: T6.7 (OUT2B), U20.31 (TX-)
unnamed: T7.4 (OUT1A), U30.32 (TX+)
unnamed: R31.1, T7.5 (OUT1B)
unnamed: C31.1, T7.6 (OUT2A)
unnamed: T7.7 (OUT2B), U30.31 (TX-)
unnamed: T8.4 (OUT1A), U40.32 (TX+)
unnamed: R41.1, T8.5 (OUT1B)
unnamed: C41.1, T8.6 (OUT2A)
unnamed: T8.7 (OUT2B), U40.31 (TX-)
unnamed: C90.1, U1.26 (PIO0_8)
unnamed: TP9.1, U1.25 (PIO0_9)
unnamed: C92.1, C94.1, U2.7 (XTI/REF_CLK), Y1.1
unnamed: C91.2, U2.6 (XTO), Y1.3
unnamed: R3.2, TP10.1, U3.5 (WP)
unnamed: L3.1, U4.8 (LX1)
unnamed: L4.1, U4.2 (LX2)
unnamed: R98.1, R99.2, U5.3 (A)
unnamed: TP1.1, U10.34 (AESOUT)
unnamed: TP5.1, U10.14 (MUTE), U10.15 (~RDY)
unnamed: C16.1, U10.8 (RX4-)
unnamed: U10.45 (SDOUTB), U10.46 (SDINB)
unnamed: R12.2, U10.11 (~LOCK)
unnamed: TP6.1, U20.14 (MUTE), U20.15 (~RDY)
unnamed: C26.1, U20.8 (RX4-)
unnamed: U20.45 (SDOUTB), U20.46 (SDINB)
unnamed: R25.1, U20.40 (SDOUTA)
unnamed: R22.2, U20.11 (~LOCK)
unnamed: TP7.1, U30.14 (MUTE), U30.15 (~RDY)
unnamed: C36.1, U30.8 (RX4-)
unnamed: R32.2, U30.11 (~LOCK)
unnamed: TP8.1, U40.14 (MUTE), U40.15 (~RDY)
unnamed: C46.1, U40.8 (RX4-)
unnamed: R45.1, U40.40 (SDOUTA)
unnamed: R42.2, U40.11 (~LOCK)
unnamed: L51.2, U51.1 (SW)
unnamed: C53.2, U52.2 (G)
unnamed: C56.2, R57.2, U53.2 (-)
unnamed: L61.2, U61.1 (SW)
unnamed: C63.2, U62.2 (G)
unnamed: C66.2, R67.2, U63.2 (-)
unnamed: L71.2, U71.1 (SW)
unnamed: C73.2, U72.2 (G)
unnamed: C76.2, R77.2, U73.2 (-)
unnamed: L81.2, U81.1 (SW)
unnamed: C83.2, U82.2 (G)
unnamed: C86.2, R87.2, U83.2 (-)

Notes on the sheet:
Populate R15 & R17 only when Control processor is not fitted.
AES42 supply and remote control (optional)
AES3 receivers/transmitters and SRC for channels B-D (optional)
ID EEPROM
Control processor (optional)
Clock synthesizer (optional)
Pullups for this I2C port are on the base board.
Debug Pod

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
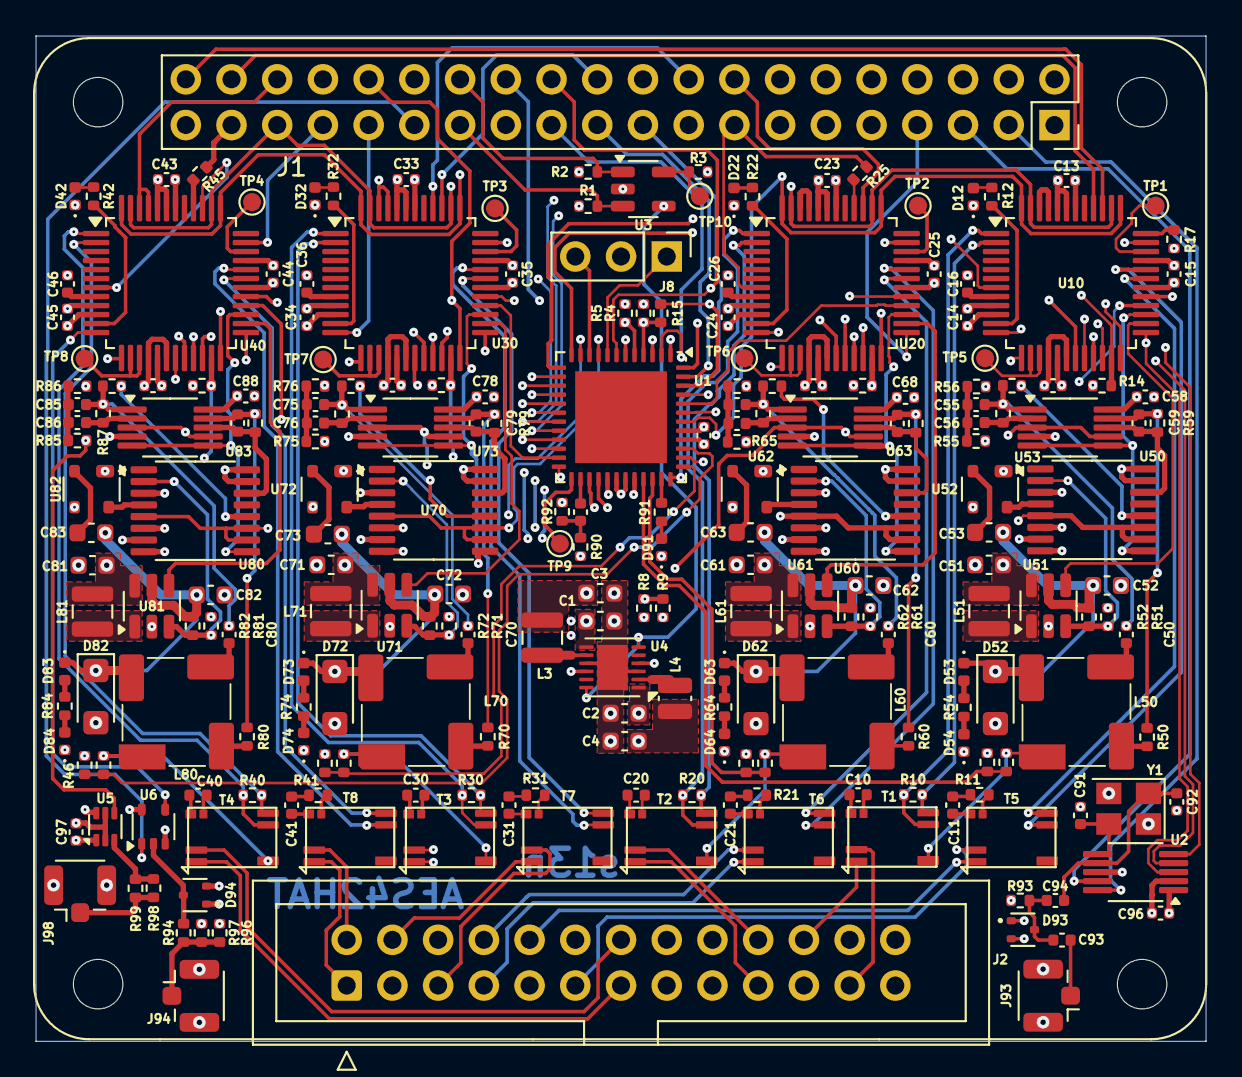
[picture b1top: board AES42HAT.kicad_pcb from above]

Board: 6 copper layers, 65.0 x 55.8 mm, 232 parts (0 on the bottom side), 226 nets.

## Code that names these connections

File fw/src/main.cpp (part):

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
static lpc865::Ftm::Parameters const ftm0par{ .ps=3, .clks=1, .mod=0xFFFF
    , .ch = {
        { .mode=::Ftm::capturePos },    // BLS time stamping
        {},                             // unused    
        { .mode=::Ftm::captureNeg },    // INTA time stamping
        { .mode=::Ftm::captureNeg },    // INTB time stamping
        { .mode=::Ftm::captureNeg },    // INTC time stamping
        { .mode=::Ftm::captureNeg }     // INTD time stamping
    }
};
static lpc865::Ftm::Parameters const ftm1par{ .ps=1, .clks=1, .mod=39999
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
